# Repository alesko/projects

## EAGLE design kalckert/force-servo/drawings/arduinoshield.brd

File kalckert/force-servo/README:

Communication with the Arduino board is done with the following settings.
Baudrate 9600
8 Data Bits
No Parity
One Stop Bit

The commands are formated as follows:
C#;
where C is the command character, # are the data character(s), and ; is the end of message.
Example; D2500; set the duration of a force pushing task to 2500 ms. 

N - Number of repertions of the trial. Default is 1.
A - Selects array or sensor imput to produce force. A0; set it to ?? to be implemented
D - Duration in ms, default is 3000 ms.
L - Delay beteen sensed force and produced force (not impelemened), default is 0 ms.
P - Pause between force pushing tasks duration, default is 1500.
E - Element number to set, default is 0.
F - Desiderd force, will be assigned to the current element (set element with the E command). Default is 0.
I - Number of force elemnts in the array. Maximum number is 128. Default is 24.

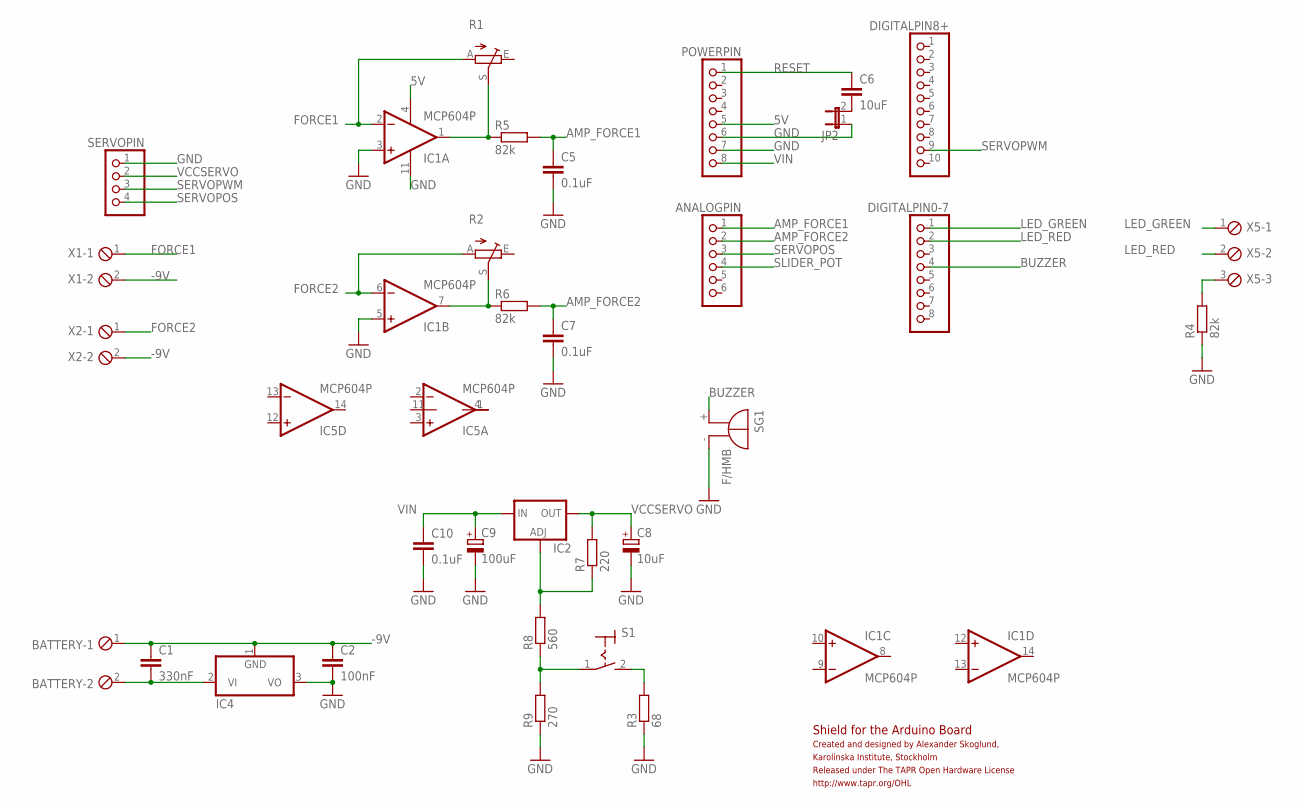
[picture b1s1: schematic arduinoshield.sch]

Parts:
ANALOGPIN: PINHD-1X6; 1X06
BATTERY: MPT2; 2POL254
C1: 330nF; C025-025X050
C2: 100nF; C025-025X050
C5, C7: 0.1uF; C025-025X050
C6: 10uF; C050-025X075
C8: 10uF; E2,5-5
C9: 100uF; E2,5-7
C10: 0.1uF; C050-025X075
DIGITALPIN0-7: PINHD-1X8; 1X08
DIGITALPIN8+: PINHD-1X10; 1X10
IC1, IC5: MCP604P; DIL14
IC2: LM317TL; 317TL
IC4: 7905T; TO220H
JP2: JP1E; JP1
POWERPIN: PINHD-1X8; 1X08
R1, R2: TRIM_EU-S64W; S64W
R3: 68; 0207/7
R4, R5, R6: 82k; 0207/7
R7: 220; 0207/7
R8: 560; 0207/7
R9: 270; 0207/7
S1: MS243
SERVOPIN: PINHD-1X4; 1X04
SG1: F/HMB
X1, X2: MPT2; 2POL254
X5: MPT3; 3POL254

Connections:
5V: IC1.4 (V+), POWERPIN.5
-9V: BATTERY.1, C1.1, C2.1, IC4.1 (GND), X1.2, X2.2
AMP_FORCE1: ANALOGPIN.1, C5.1, R5.2
AMP_FORCE2: ANALOGPIN.2, C7.1, R6.2
BUZZER: DIGITALPIN0-7.4, SG1.+
FORCE1: IC1.2 (-IN), R1.A, X1.1
FORCE2: IC1.6 (-IN), R2.A, X2.1
GND: C2.2, C5.2, C7.2, C8.-, C9.-, C10.2, IC1.3 (+IN), IC1.5 (+IN), IC1.11 (V-), IC4.3 (VO), JP2.1, POWERPIN.6, POWERPIN.7, R3.1, R4.1, R9.1, SERVOPIN.1, SG1.-
LED_GREEN: DIGITALPIN0-7.1, X5.1
LED_RED: DIGITALPIN0-7.2, X5.2
unnamed: BATTERY.2, C1.2, IC4.2 (VI)
unnamed: C6.2, JP2.2
unnamed: R3.2, S1.2 (S)
unnamed: IC5.1 (OUT), IC5.4 (V+)
unnamed: IC1.1 (OUT), R1.S, R5.1
unnamed: IC1.7 (OUT), R2.S, R6.1
unnamed: R8.1, R9.2, S1.1
unnamed: IC2.1 (ADJ), R7.1, R8.2
RESET: C6.1, POWERPIN.1
SERVOPOS: ANALOGPIN.3, SERVOPIN.4
SERVOPWM: DIGITALPIN8+.9, SERVOPIN.3
SLIDER_POT: ANALOGPIN.4
V-: IC5.11 (V-)
VCCSERVO: C8.+, IC2.2 (OUT), R7.2, SERVOPIN.2
VIN: C9.+, C10.1, IC2.3 (IN), POWERPIN.8

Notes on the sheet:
Shield for the Arduino Board
Created and designed by Alexander Skoglund,
Karolinska Institute, Stockholm
Released under The TAPR Open Hardware License
http://www.tapr.org/OHL

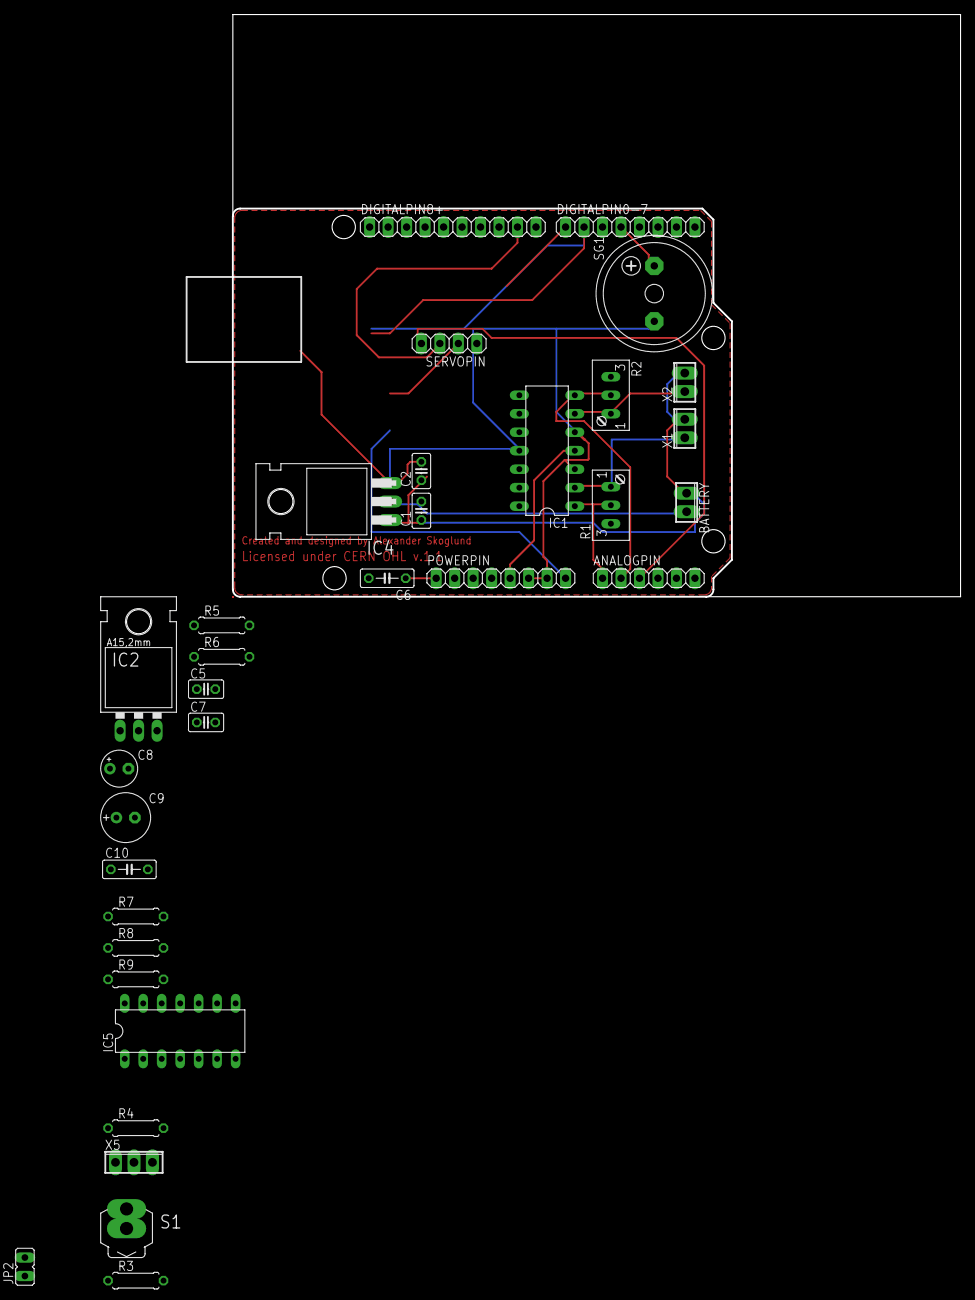
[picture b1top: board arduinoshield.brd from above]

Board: 2 copper layers, 100.0 x 80.0 mm, 33 parts (0 on the bottom side), 23 nets.

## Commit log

2012-06-29 First commit of project only containing Adreas project
2012-07-04 Folder for documentation
2012-07-04 Added eagle schematic and drawing
2012-07-05 Finnished PC board
2012-07-05 Added pdf drawing and a partlist
2012-07-06 Python program that communicates with the Arduino. Reads forces from a file, sends it to the Arduino and store reposedata in another file. Not yet complete.
2012-07-09 First version of the PCB is ready.
2012-07-09 Added licensing info to board. Tested python program on mac (tkinter only works in IDLE).
2012-07-10 Added a timestamp to the measure, ms from start of prog.
2012-07-10 Corrected force and buzzer pins to correspond to PCB.
2012-07-10 Added hardware licensing files. Updated shematic to prevent autoreset of Arduino.
2012-07-11 Updated licenses.
2012-07-12 First untested reading of floats on the Arduino.
2012-07-12 Added a calibration sequence in the arduino program.
2012-07-13 Updated calibration programs, noy yet functional
2012-07-17 Tuning the PD controller gains, not yet stable. Updated schematic with the LP filter.
2012-07-19 Keeping it up to date.
2012-08-30 Added the photodide amplifire drawings, designed for Claudio's TMS setup.
2012-08-30 Added the foot switch documentation. A MR compatible (modified Herga) pneumatic foot switch, that outputs a 'g'.
2012-09-11 New force calibration without extra contoller, rely on PID in servo.
2012-10-01 Updated power regulator
2012-10-12 Moved tapometer from its own folder to project folder and added drawings and the CERn hardware licence to the drawings.
2012-10-22 Added a planning spreadsheet.
2012-10-22 New readme file on howto install a library for the Arduino. comintrface is needed for this program.
2012-10-22 Cleaned up force-servo arduino program.
2012-10-24 Updated arduino with fault checks
2012-10-29 Added the comunication interface class.
2012-10-29 Added Hudding equimpment list.
2012-10-29 Update Huddinge equimpent spread sheet after meeting 2012-10-29.
2012-10-31 Updated project planning.

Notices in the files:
kalckert/force-servo/drawings/arduinoshield.brd:
Licensed under CERN OHL v.1.1
